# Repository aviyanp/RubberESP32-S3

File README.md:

# RubberESP32-S3
A Rubber Ducky Devboard built around an ESP32-S3-WROOM-1U Module. I built this because I really wanted to make my first devboard and it seemed like the perfect time to do so! It took way too much work, and it costs ~$90 because of Standard PCBA for the ESP32-S3, so I think it'd be better to just buy the parts needed to solder it on by hand and learn all about SMD soldering! It's definitely a learning curve trying to figure out what goes where and how to not screw up your routing so bad that you have to reverse ~4+ hours of work. I'm eventually trying to make an all-in-one mainboard for a robot that would incorporate 4 custom-made motor drivers and an ESP32-S3 controlling it all, so this is the first step in that direction! For now, I wanted something that I can easily test out and use IRL, so I decided to make a rubber ducky! It was really freaking rage-inducing, but it was all good fun and I learned a lot from it all.

---

## Images

---

| Comment               | Designator                | Footprint                       | LCSC     | Quantity | Price (Based on MOQ) | Notes                                                                                                                   |
|-----------------------|---------------------------|---------------------------------|----------|----------|----------------------|-------------------------------------------------------------------------------------------------------------------------|
| 5.1K                  | R12,R13                   | R0603                           | C14677   | 4        | $0.12                |                                                                                                                         |
| 10K                   | R10,R11,R3,R5,R6,R7,R8,R9 | R0603                           | C15401   | 16       | $0.09                |                                                                                                                         |
| 100nF                 | C2,C4                     | C0603                           | C1591    | 4        | $0.28                |                                                                                                                         |
| 1uF                   | C3                        | C0603                           | C1592    | 2        | $0.17                |                                                                                                                         |
| 100R                  | R4                        | R0603                           | C25201   | 2        | $0.1                 |                                                                                                                         |
| 22uF                  | C6                        | CAP-SMD_BD6.3-L6.6-W6.6-FD      | C267472  | 2        | $0.64                |                                                                                                                         |
| TYPE-C 16PIN 2MD(073) | USB1                      | USB-C-SMD_TYPE-C-6PIN-2MD-073   | C2765186 | 2        | $1.1                 |                                                                                                                         |
| 22uF                  | C1                        | C1210                           | C2918511 | 2        | $0.4                 |                                                                                                                         |
| ESP32-S3-MINI-1U      | U1                        | ESP32-S2-MINI-1U                | C2980296 | 3        | $10.8                | I have 3 because I'd otherwise get a $3 fee and it costs around that and it's pretty easy to mess up when soldering it. |
| AMS1117-3.3           | U2                        | SOT-223-3_TabPin2               | C347222  | 2        | $0.2                 |                                                                                                                         |
| TF PUSH               | Card1                     | TF-SMD_TF-PUSH                  | C393941  | 2        | $0.55                |                                                                                                                         |
| SW_SPST               | SW1,SW2                   | SW-SMD_L3.9-W3.0-P4.45          | C455280  | 4        | $0.46                |                                                                                                                         |
| 10uF                  | C5                        | CAP-SMD_BD6.3-L6.6-W6.6-FD      | C72482   | 2        | $0.45                |                                                                                                                         |
| Conn_01x02            | J2                        | PinHeader_1x02_P2.54mm_Vertical |          | 1        | $5.49                | Price includes other headers                                                                                            |
| Conn_01x02            | J1                        | PinHeader_1x02_P2.54mm_Vertical |          | 1        |                      |                                                                                                                         |
| Conn_01x08            | J3                        | PinHeader_1x08_P2.54mm_Vertical |          | 1        |                      |                                                                                                                         |
| Solder Paste          |                           |                                 |          | 1        | $13.95               |                                                                                                                         |
| Solder                |                           |                                 |          | 1        | $8                   |                                                                                                                         |
| PCB                   |                           |                                 |          | 5        | $2                   |                                                                                                                         |
| Stencil               |                           |                                 |          | 1        | $7                   |                                                                                                                         |
| Hotplate              |                           |                                 |          | 1        | $15                  |                                                                                                                         |
| JLCPCB Shipping       |                           |                                 |          |          | $18.63               |                                                                                                                         |
| LCSC Shipping         |                           |                                 |          |          | $10.45               |                                                                                                                         |
| Amazon Shipping       |                           |                                 |          |          | $9                   |                                                                                                                         |

## Total Cost: $104.88

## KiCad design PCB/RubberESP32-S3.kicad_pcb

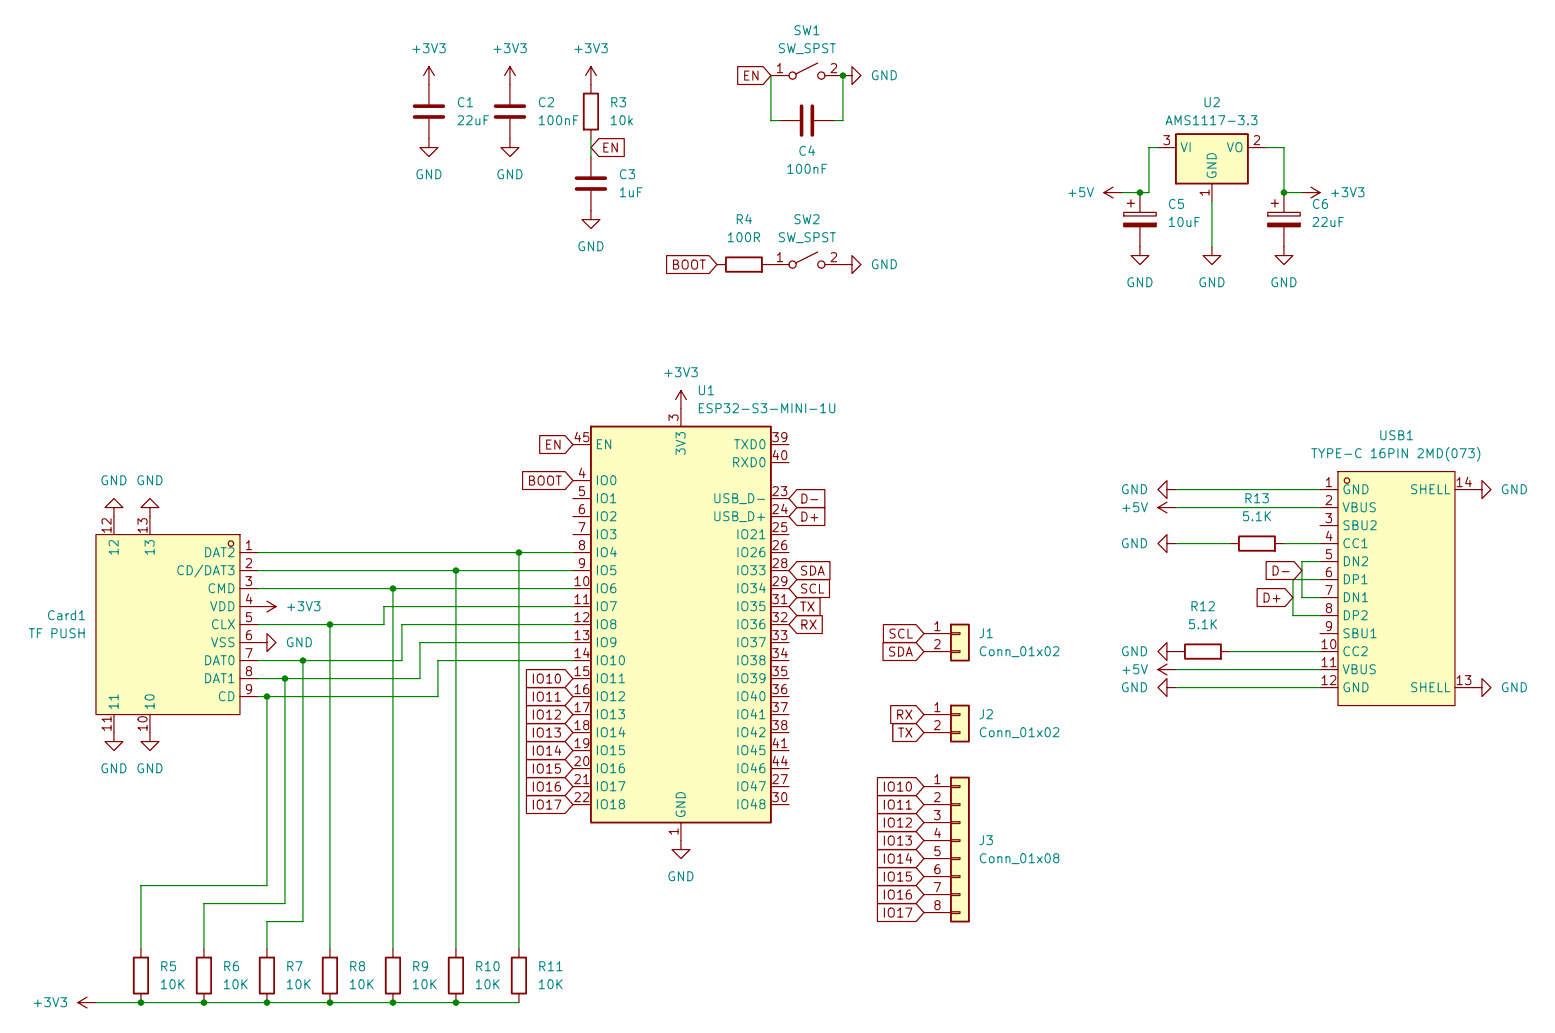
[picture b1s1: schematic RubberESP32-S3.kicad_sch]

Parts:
C1: 22uF; C1210
C2, C4: 100nF; C0603
C3: 1uF; C0603
C5: 10uF; CAP-SMD_BD6.3-L6.6-W6.6-FD
C6: 22uF; CAP-SMD_BD6.3-L6.6-W6.6-FD
Card1: TF PUSH; TF-SMD_TF-PUSH; LCSC Part C393941
J1, J2: Conn_01x02; PinHeader_1x02_P2.54mm_Vertical
J3: Conn_01x08; PinHeader_1x08_P2.54mm_Vertical
R3: 10k; R0603
R4: 100R; R0603
R5, R6, R7, R8, R9, R10, R11: 10K; R0603
R12, R13: 5.1K; R0603
SW1, SW2: SW_SPST; SW-SMD_L3.9-W3.0-P4.45
U1: ESP32-S3-MINI-1U; ESP32-S2-MINI-1U
U2: AMS1117-3.3; SOT-223-3_TabPin2
USB1: TYPE-C 16PIN 2MD(073); USB-C-SMD_TYPE-C-6PIN-2MD-073; LCSC Part C2765186

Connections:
+3V3: C1.1, C2.1, C6.1, Card1.4 (VDD), R3.1, R5.1, R6.1, R7.1, R8.1, R9.1, R10.1, R11.1, U1.3 (3V3), U2.2 (VO)
+5V: C5.1, U2.3 (VI), USB1.2 (VBUS), USB1.11 (VBUS)
BOOT: R4.1, U1.4 (IO0)
D+: U1.24 (USB_D+), USB1.6 (DP1), USB1.8 (DP2)
D-: U1.23 (USB_D-), USB1.5 (DN2), USB1.7 (DN1)
EN: C3.1, C4.2, R3.2, SW1.1 (A), U1.45 (EN)
GND: C1.2, C2.2, C3.2, C4.1, C5.2, C6.2, Card1.6 (VSS), Card1.10, Card1.11, Card1.12, Card1.13, R12.1, R13.1, SW1.2 (B), SW2.2 (B), U1.1 (GND), U1.2 (GND), U1.42 (GND), U1.43 (GND), U1.46 (GND), U1.47 (GND), U1.48 (GND), U1.49 (GND), U1.50 (GND), U1.51 (GND), U1.52 (GND), U1.53 (GND), U1.54 (GND), U1.55 (GND), U1.56 (GND), U1.57 (GND), U1.58 (GND), U1.59 (GND), U1.60 (GND), U1.61 (GND), U1.62 (GND), U1.63 (GND), U1.64 (GND), U1.65 (GND), U2.1 (GND), USB1.1 (GND), USB1.12 (GND), USB1.13 (SHELL), USB1.14 (SHELL)
IO10: J3.1, U1.15 (IO11)
IO11: J3.2, U1.16 (IO12)
IO12: J3.3, U1.17 (IO13)
IO13: J3.4, U1.18 (IO14)
IO14: J3.5, U1.19 (IO15)
IO15: J3.6, U1.20 (IO16)
IO16: J3.7, U1.21 (IO17)
IO17: J3.8, U1.22 (IO18)
unnamed: Card1.9 (CD), R5.2, U1.14 (IO10)
unnamed: Card1.2 (CD/DAT3), R10.2, U1.9 (IO5)
unnamed: Card1.5 (CLX), R8.2, U1.11 (IO7)
unnamed: Card1.3 (CMD), R9.2, U1.10 (IO6)
unnamed: Card1.7 (DAT0), R7.2, U1.12 (IO8)
unnamed: Card1.8 (DAT1), R6.2, U1.13 (IO9)
unnamed: Card1.1 (DAT2), R11.2, U1.8 (IO4)
unnamed: R4.2, SW2.1 (A)
unnamed: R13.2, USB1.4 (CC1)
unnamed: R12.2, USB1.10 (CC2)
RX: J2.1, U1.32 (IO36)
SCL: J1.1, U1.29 (IO34)
SDA: J1.2, U1.28 (IO33)
TX: J2.2, U1.31 (IO35)

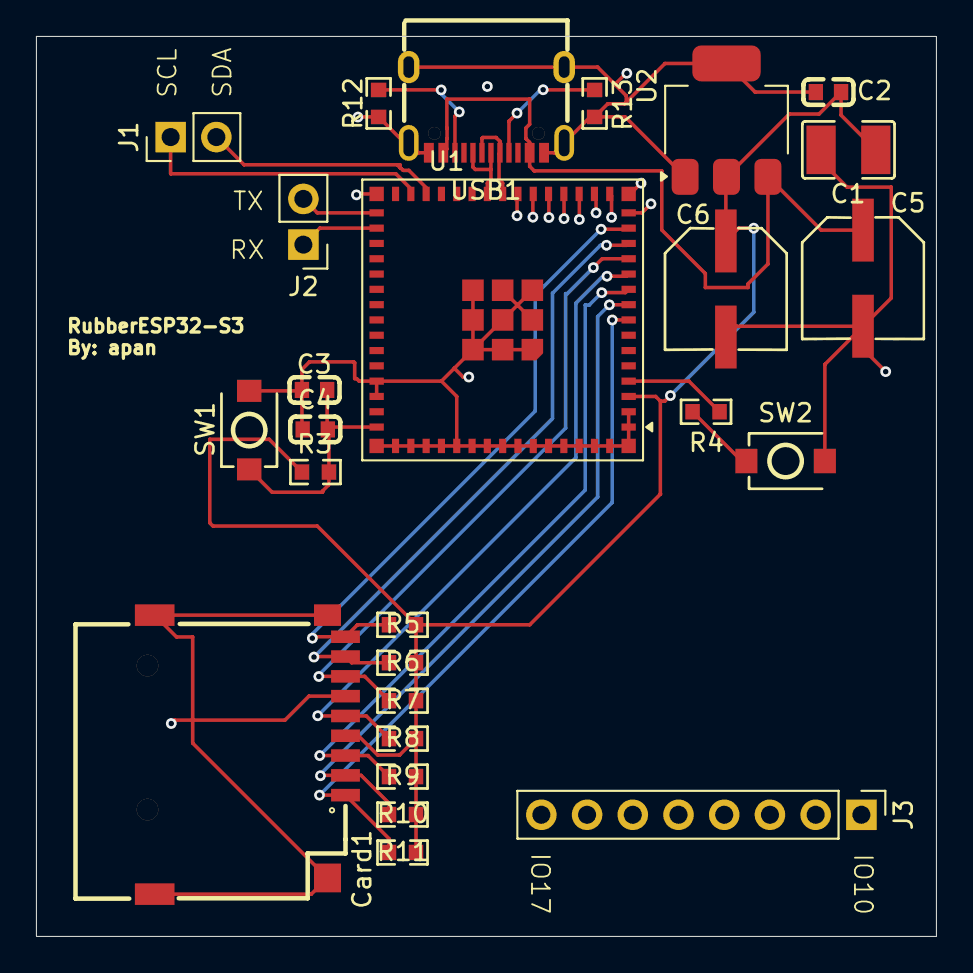
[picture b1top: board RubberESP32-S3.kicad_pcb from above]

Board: 4 copper layers, 50.0 x 50.0 mm, 26 parts (0 on the bottom side), 29 nets.

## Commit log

2025-07-19 Rename BackupRubberESP32-S3 copy.kicad_pcb to RubberESP32-S3.kicad_pcb
